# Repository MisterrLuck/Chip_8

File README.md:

# Chip 8

A Chip 8 emulator written in C++ with the Raylib graphics library.

Aside from the emulator, it currently includes a text to rom converter (to write programs in hexadecimal easily), a custom debugger, and an assembler.

This is my first emulation project to get me into the genre. It has been super fun to make, and there is a great community surrounding it.

## Table of Contents

- [Features](#features)
    - [Emulator](#emulator)
        - [Configuration](#configuration)
    - [Debugger](#debugger)
    - [Assembler](#assembler)
    - [Hex Code](#hex-code)
- [Building](#building)
    - [Requirements](#requirements)
    - [Compilation](#compiling-from-source)
- [Thanks](#thanks)
- [What's Next](#whats-next)

## Features

### Emulator

The Emulator is run fully from the command line. To run a program, just provide it as an argument.

```
./Chip_8 myRom.ch8
```

You can also change the Chip 8 version with the configuration flag.

```
./Chip_8 -c chip-48 myRom.ch8
```

#### Configuration

A list of all the current configuration options can be found [here](docs/configuration.md).

### Debugger

You can also debug programs using the custom debugger. Just add the debug flag when running.

``` bash
./Chip_8 -d myRom.ch8
```

This will make the program pause after every instruction, and wait for a command input.
A list of all the instructions for the debugger can be found [here](docs/debugger.md).

### Assembler

An assembler is also provided separately from the emulator.

It is a custom made assembly language and **not** an octo assembler. The reference can be found [here](docs/assembly.md).

When it's run with only an input file, the output will default to `out.ch8`.

```
./Assembler myRom.asm
```

You can specify an output file using the `-o` flag.

```
./Assembler myRom.asm -o myRom.ch8
```

Changing the configuration works the same way as it does for the emulator.

```
./Assembler -c chip-8 myRom.asm -o myRom.ch8
```

### Hex Code

You can use the `scripts/code_to_rom.py` file to convert your code from text to a binary file, that you can run.

```bash
python code_to_rom.py
```

If you want to make it easier to recompile you programs quickly, use the command line arguments instead.

```bash
python code_to_rom.py input_file.txt output_file.ch8
```

Or even better, if you want them to have the same name, just provide the input file.

```bash
python code_to_rom.py myRom.txt
```

This will write to myRom.ch8.

The converter also allows you to document your code with comments, using `#`.

## Building

Compilation has currently only been tested for Linux. Specifically on Ubuntu with an Intel processor.

> If you have tested building on another device, please let me know.

### Requirements

Make sure you have all the requirements before building.

- C++17
- CMake (Minimum Version 4.2)
- [raylib](https://github.com/raysan5/raylib#build-and-installation)
- [CLI11](https://github.com/cliutils/cli11)

Raylib is installed to the system and found through CMake. CLI11 should be just the header file, installed to the `include/utils` directory.

### Compiling from Source

After installing all the requirements, you can build the Emulator and Assembler using CMake.

```bash
mkdir build
cd build
cmake ..
make
```

Run the emulator with your desired ROM as an input. A test program, `roms/default_program.ch8`, is provided to ensure everything was set up correctly. 

## Thanks

Thanks to Tobias V. I. Langhoff and his [blog post](https://tobiasvl.github.io/blog/write-a-chip-8-emulator/) on making a Chip 8 emulator.

Thanks to Timendus for his [Chip-8 Test Suite](https://github.com/Timendus/chip8-test-suite) which fixed most issues.

Thanks to Gulrak for help debugging and also for inspiration on his emulator [Cadmium](https://github.com/gulrak/cadmium).

Thanks to Various people in the EmuDev discord server for guidance.

## Whats Next

Some things I want to add in the future

 - Improve the debugger to have a separate window running at once, inspired by [massung](https://github.com/massung/CHIP-8), [Austin Morlan](https://code.austinmorlan.com/austin/2019-chip8-emulator), or [Gulrak's Cadmium](https://github.com/gulrak/cadmium).
 - Possibly move away from Raylib to learn a more common graphics library like SDL.
 - Add proper [SUPER-CHIP](https://johnearnest.github.io/Octo/docs/SuperChip.html) support with the larger screen and extra instructions, instead of just the inconsistencies in existing instructions.
 - Maybe even adding [XO-CHIP](https://johnearnest.github.io/Octo/docs/XO-ChipSpecification.html) functionality.
 - Eventually work in as many CHIP 8 versions as possible.

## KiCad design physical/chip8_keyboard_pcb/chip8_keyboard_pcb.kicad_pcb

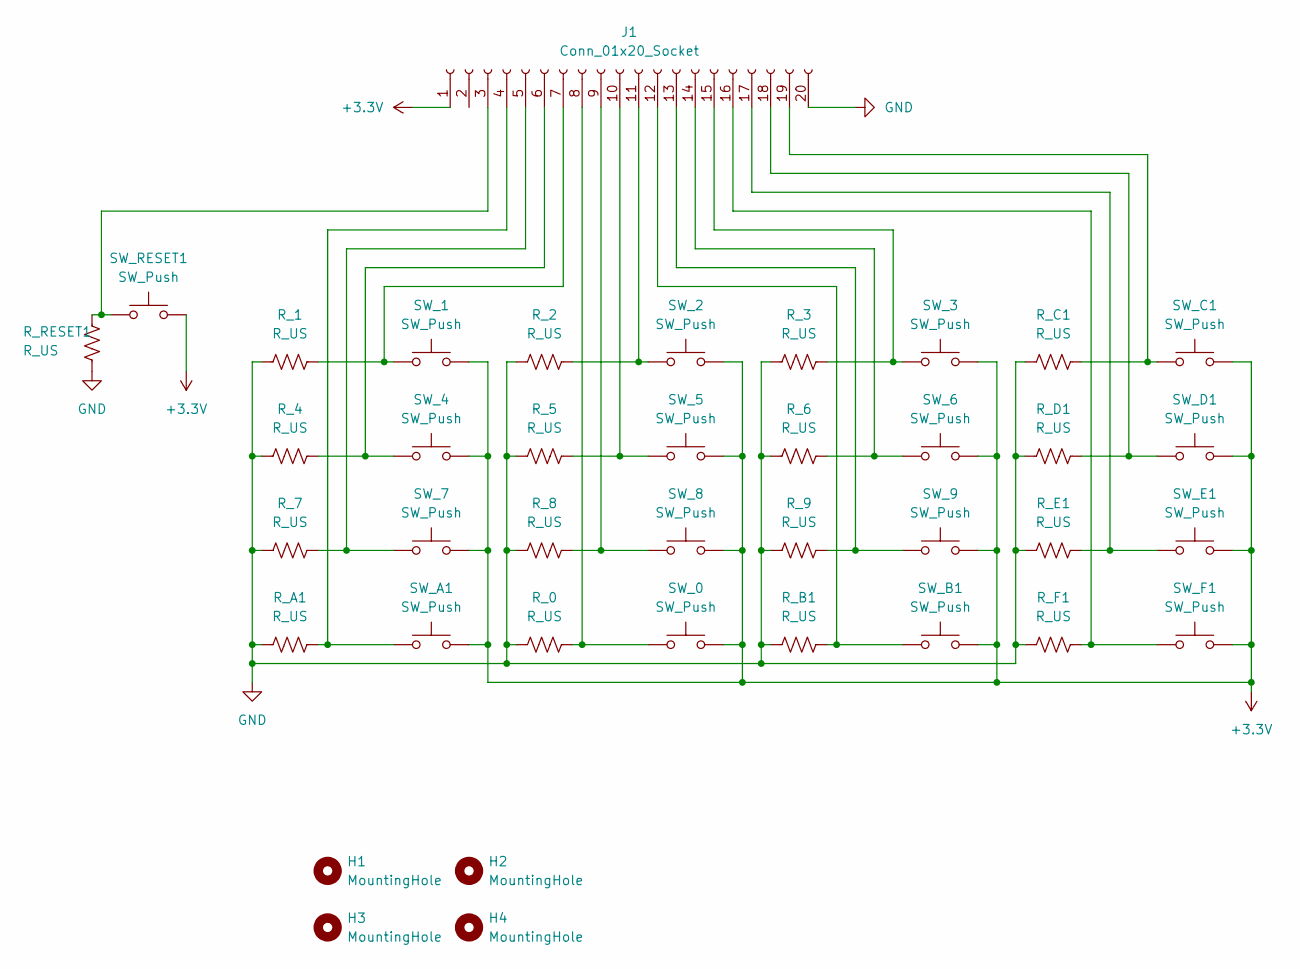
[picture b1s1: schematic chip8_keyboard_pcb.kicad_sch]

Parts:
H1, H2, H3, H4: MountingHole; MountingHole_4.3mm_M4
J1: Conn_01x20_Socket; PinSocket_1x20_P2.54mm_Vertical
R_0, R_1, R_2, R_3, R_4, R_5, R_6, R_7, R_8, R_9: R_US; R_Axial_DIN0204_L3.6mm_D1.6mm_P5.08mm_Horizontal
R_A1: R_US; R_Axial_DIN0204_L3.6mm_D1.6mm_P5.08mm_Horizontal
R_B1: R_US; R_Axial_DIN0204_L3.6mm_D1.6mm_P5.08mm_Horizontal
R_C1: R_US; R_Axial_DIN0204_L3.6mm_D1.6mm_P5.08mm_Horizontal
R_D1: R_US; R_Axial_DIN0204_L3.6mm_D1.6mm_P5.08mm_Horizontal
R_E1: R_US; R_Axial_DIN0204_L3.6mm_D1.6mm_P5.08mm_Horizontal
R_F1: R_US; R_Axial_DIN0204_L3.6mm_D1.6mm_P5.08mm_Horizontal
R_RESET1: R_US; R_Axial_DIN0204_L3.6mm_D1.6mm_P5.08mm_Horizontal
SW_0, SW_1, SW_2, SW_3, SW_4, SW_5, SW_6, SW_7, SW_8, SW_9: SW_Push; SW_Cherry_MX_1.25u_PCB
SW_A1: SW_Push; SW_Cherry_MX_1.25u_PCB
SW_B1: SW_Push; SW_Cherry_MX_1.25u_PCB
SW_C1: SW_Push; SW_Cherry_MX_1.25u_PCB
SW_D1: SW_Push; SW_Cherry_MX_1.25u_PCB
SW_E1: SW_Push; SW_Cherry_MX_1.25u_PCB
SW_F1: SW_Push; SW_Cherry_MX_1.25u_PCB
SW_RESET1: SW_Push; SW_PUSH_6mm

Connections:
+3.3V: J1.1, SW_0.2, SW_1.2, SW_2.2, SW_3.2, SW_4.2, SW_5.2, SW_6.2, SW_7.2, SW_8.2, SW_9.2, SW_A1.2, SW_B1.2, SW_C1.2, SW_D1.2, SW_E1.2, SW_F1.2, SW_RESET1.2
GND: J1.20, R_0.1, R_1.1, R_2.1, R_3.1, R_4.1, R_5.1, R_6.1, R_7.1, R_8.1, R_9.1, R_A1.1, R_B1.1, R_C1.1, R_D1.1, R_E1.1, R_F1.1, R_RESET1.2
unnamed: J1.3, R_RESET1.1, SW_RESET1.1
unnamed: J1.4, R_A1.2, SW_A1.1
unnamed: J1.5, R_7.2, SW_7.1
unnamed: J1.6, R_4.2, SW_4.1
unnamed: J1.7, R_1.2, SW_1.1
unnamed: J1.8, R_0.2, SW_0.1
unnamed: J1.9, R_8.2, SW_8.1
unnamed: J1.10, R_5.2, SW_5.1
unnamed: J1.11, R_2.2, SW_2.1
unnamed: J1.12, R_B1.2, SW_B1.1
unnamed: J1.13, R_9.2, SW_9.1
unnamed: J1.14, R_6.2, SW_6.1
unnamed: J1.15, R_3.2, SW_3.1
unnamed: J1.16, R_F1.2, SW_F1.1
unnamed: J1.17, R_E1.2, SW_E1.1
unnamed: J1.18, R_D1.2, SW_D1.1
unnamed: J1.19, R_C1.2, SW_C1.1

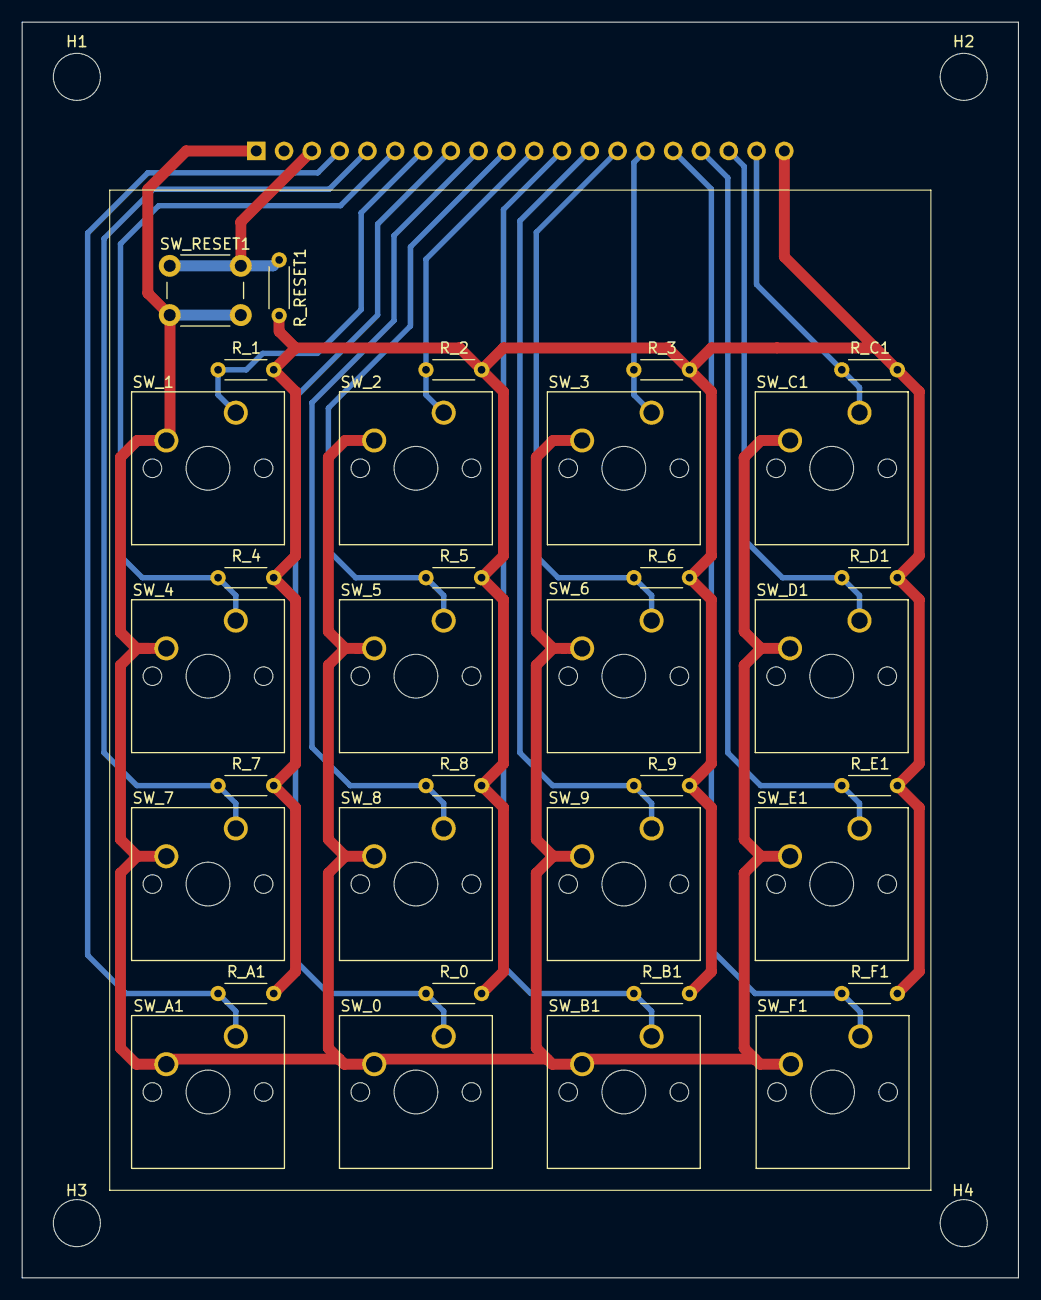
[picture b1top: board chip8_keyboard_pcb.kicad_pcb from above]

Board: 2 copper layers, 91.0 x 114.8 mm, 39 parts (1 on the bottom side), 19 nets.
